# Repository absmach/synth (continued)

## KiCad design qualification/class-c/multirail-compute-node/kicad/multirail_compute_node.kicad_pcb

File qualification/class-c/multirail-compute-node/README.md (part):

# Multi-rail compute node with USB-C and a 5 to 12 V input (Class C, not a case-4 pass)

An STM32F103C8 microcontroller with a 128 Mbit SPI flash and a USB-C receptacle, on a four-layer board of 85.0 x 63.0 mm. It is powered from a 5 to 12 V DC header or from USB VBUS. A 4 A buck converter, three linear rails, a load switch that sequences them and an expansion header complete the board.

It answers #331 under #40: a board whose thermal paths, assembly access and DFM limits are declared and visible in the exported output, made by an agent driving `synth mcp`. It does not claim a case-4 pass. The items in "Not verified by Synth" are open.

The prompt to reproduce the board is in [`PROMPT.md`](PROMPT.md), written from the finished board. The prompts the agent ran are in the history at `72b6f250`.

## The board

### Parts

| Group                | Parts                                                                                                                                                                                                                                                                                                                                                                                      |
| -------------------- | ------------------------------------------------------------------------------------------------------------------------------------------------------------------------------------------------------------------------------------------------------------------------------------------------------------------------------------------------------------------------------------------ |
| DC input (5 to 12 V) | `J2` 1x2 header; `F1` Bourns MF-MSMF110/16-2 (1.1 A hold, 16 V); `D1` Littelfuse SMAJ15A TVS; `D2` Vishay SS36 Schottky reverse-blocking diode (60 V, 0.75 V at 3 A)                                                                                                                                                                                                                       |
| USB input            | `J1` Korean Hroparts TYPE-C-31-M-12 receptacle, flush on the left edge, 5 V only (D+ and D- go to the MCU); `R11` and `R12` 5.1 k CC pull-downs; `F2` Bourns MF-MSMF110/16-2; `D3` Nexperia PTVS6V0S1UR; `D4` Diodes 1N5819HW-7-F ORs VBUS into the buck input (40 V, 450 mV at 1 A); `D5` and `D6` Nexperia PESD5V0S1BA on D+ and D-; `D11` and `D12` the same part on CC1 and CC2; `C30` |
| Buck 3.6 V           | `U1` Texas Instruments LMR33640ADDA (3.8 to 36 V in, 4 A, internal compensation, EN tied to VIN); `L1` Bourns SRN6045TA-6R8M 6.8 uH (Isat 5.7 A, Idc 3.6 A); input `C1`, `C2` 10 uF 25 V and `C3` 220 nF; output `C4`, `C5` 22 uF 25 V; `C6` 100 nF bootstrap; `C7` 1 uF VCC bypass; feedback divider `R2` 10 k and `R3` 3.83 k; `R1` pulls PG up                                          |
| 3.3 V rail           | `U2` TI LP5907MFX-3.3 (3.3 V, 250 mA) with `C8`, `C9`                                                                                                                                                                                                                                                                                                                                      |
| Load switch          | `U5` TI TPS22918DBVR (53 mohm at 3.3 V) with `C12`, `C13` (1 nF, rise time) and `C14`; enable delay `R16` 100 k and `C17` 100 nF                                                                                                                                                                                                                                                           |
| 1.8 V rail           | `U3` Diodes AP2112K-1.8 (600 mA, no minimum load) behind the switch, with `C10`, `C11`                                                                                                                                                                                                                                                                                                     |
| 1.2 V rail           | `U4` TI TLV70012DDCR (1.2 V, 200 mA, DDC package) enabled by the 1.8 V rail, with `C15`, `C16`                                                                                                                                                                                                                                                                                             |
| Compute core         | `U6` STMicroelectronics STM32F103C8T6 (LQFP-48) with decoupling `C20` to `C25`; `Y1` JYJE 3TJ480000FYLBC 8 MHz crystal with `C26`, `C27` 10 pF; reset `R9`, `C28`, `SW1`; `R10` pulls BOOT0 low; `R13` 1.5 k USB D+ pull-up; `J3` 1x5 SWD header                                                                                                                                           |
| Memory               | `U7` Winbond W25Q128JVSIQ, SOIC-8 208 mil, on SPI1 (`PA4` to `PA7`) with `C29`, `R14`, `R15`                                                                                                                                                                                                                                                                                               |
| Indicators           | `D7` red (3.6 V), `D8` green (3.3 V), `D9` and `D10` yellow user LEDs, with `R5` to `R8`                                                                                                                                                                                                                                                                                                   |
| Expansion            | `J4` Harwin M20-9990846 1x8 header: 3.6 V gated, 3.3 V, 1.8 V, 1.2 V, two GPIOs, two grounds                                                                                                                                                                                                                                                                                               |
| Fabrication features | Test points `TP1` to `TP9`, all on the bottom side of the board; fiducials `FID1` to `FID3`; two M2.5 mounting holes at opposite corners, each 4.0 mm from its two board edges                                                                                                                                                                                                                                                                                                            |

### Layout

| Item                    | Value                                                                                                                                                                         |
| ----------------------- | ----------------------------------------------------------------------------------------------------------------------------------------------------------------------------- |
| Outline                 | 85.0 x 63.0 mm, declared in the source (`outline 85mm x 63mm`)                                                                                                                                                                |
| Copper layers           | 4                                                                                                                                                                             |
| Stackup                 | 1.59 mm total (board file); `manufacturer "jlc-filled-via"` with `requires via_in_pad` (resin-filled, capped vias for the exposed-pad vias); JLCPCB 7628 stack, 1.065 mm core |
| Parts in the BOM        | 85 lines: 71 parts and 14 board features (test points, fiducials, mounting holes)                                                                                             |
| Parts placed in the CPL | 74                                                                                                                                                                            |
| Nets                    | 42, all routed                                                                                                                                                                |
| Track segments          | 456                                                                                                                                                                           |
| Vias                    | 88: 21 x 0.46/0.2 mm and 67 x 0.6/0.3 mm                                                                                                                                      |
| Track length            | 1270.8 mm                                                                                                                                                                     |
| Zones and planes        | `GND` poured on all four layers; the rails are tracks, not planes; `hot_buck` keepout rule area on `U1`; 2.75 mm screw-head zones on `H1` and `H2`                            |
| Fab package             | `fab/gerbers.zip` (16 files), `fab/bom.csv`, `fab/cpl.csv`; every file is in `SHA256SUMS`                                                                                     |
| 3D models               | `models/` holds the STEP body of every part the board references and the board model `multirail_compute_node.step`. The board file reaches them by the relative path `${KIPRJMOD}/../models/`. Mounting holes and fiducials have no body. `J1` uses the HRO TYPE-C-31-M-12 STEP from github.com/ai03-2725/Type-C.pretty (the repository states no licence), placed to match KiCad's footprint. Any other part that KiCad's library has no model for is a simplified box of its envelope. |
| Schematic               | `images/schematic.pdf`: vector pages, one per sheet, plotted by `kicad-cli sch export pdf`. |

### Checks

| Check                              | Result                               | Notes                                                                                                 |
| ---------------------------------- | ------------------------------------ | ----------------------------------------------------------------------------------------------------- |
| KiCad DRC (10.0.8, --refill-zones) | 0 errors, 7 warnings, 0 unconnected  | The warnings are 4 `silk_over_copper` and 3 `lib_footprint_mismatch` on the fiducials                                                                 |
| KiCad ERC (10.0.8)                 | 0 errors, 63 warnings, 0 unconnected | 62 `lib_symbol_issues`, 1 `lib_symbol_mismatch`                                                       |
| KiCad DRC with the library tables  | 85 `lib_footprint_mismatch`          | The exporter cuts back the silkscreen (#425); pads and courtyards match the library                   |
| Gerbers                            | Plotted from refilled zones          | Plotted from the refilled zones of the committed board                                                |
| `synth validate`                   | 0 errors, 40 warnings                | 17 are schematic-layout findings: 9 `E-SYNTH-SCHEM-003`, 7 `E-SYNTH-SCHEM-001`, 1 `E-SYNTH-SCHEM-004` |
| Schematic-layout findings          | Accepted as a group                  | They concern the drawing of the generated schematic, not the netlist or the board                     |
| `synth validate` warning count     | Varies                               | The count changes with the Synth version                                                              |

### Design figures

| Area             | Item                     | Value                                                                                                                                                                | Basis                                                                              |
| ---------------- | ------------------------ | -------------------------------------------------------------------------------------------------------------------------------------------------------------------- | ---------------------------------------------------------------------------------- |
| Protection       | `D1` standoff            | 15 V, above the 12.6 V maximum input (12 V +5 %)                                                                                                                     | Littelfuse SMAJ15A datasheet; calculated                                           |
| Protection       | `D1` clamp               | 24.4 V at 16.4 A, below the 36 V input maximum of `U1`                                                                                                               | Littelfuse SMAJ15A and TI LMR33640 datasheets                                      |
| Protection       | `D3` standoff            | 6.0 V, above the 5.25 V maximum VBUS                                                                                                                                 | Nexperia PTVS6V0S1UR datasheet                                                     |
| Power            | Buck output voltage      | 1.0 V x (1 + 10 / 3.83) = 3.611 V                                                                                                                                    | Calculated; 1.0 V feedback reference from the TI LMR33640 datasheet                |
| Power            | Inductor ripple          | (12 - 3.611) x (3.611 / 12) / (6.8 uH x 400 kHz) = 0.93 A at 12 V in, 400 kHz                                                                                        | Calculated                                                                         |
| Power            | Load switch enable delay | `R16` 100 k x `C17` 100 nF = 10 ms                                                                                                                                   | Calculated                                                                         |
| Power            | Rail sequence            | 3.3 V first; then the switch passes 3.6 V to the 1.8 V regulator; then 1.8 V enables the 1.2 V regulator                                                             | Netlist in the .synth source                                                       |
| Power            | Sequenced rail loads     | The 1.8 V and 1.2 V rails feed only `J4` and test points; the STM32F103C8 runs from 3.3 V alone, so the sequencing protects no device on this board                  | Netlist in the .synth source                                                       |
| Power            | USB-only input to `U1`   | At 4.75 V VBUS and 1.0 A, `F2` (0.21 ohm) drops 0.21 V and `D4` drops 0.45 V, so `U1` sees 4.09 V                                                                    | Calculated                                                                         |
| Power            | USB-only buck margin     | `U1` needs 3.76 V for a 3.611 V output (150 mV dropout at 1 A); margin 0.33 V                                                                                        | TI LMR33640 datasheet; calculated                                                  |
| Power            | USB-only LDO margin      | The LP5907 needs 3.55 V (250 mV dropout at 250 mA); margin 61 mV                                                                                                     | TI LP5907 datasheet; calculated                                                    |
| Power            | Power good               | `PG_3V6` goes to `PA0` of `U6`, pulled up by `R1` 10 k to `V3V3` (0.33 mA when low)                                                                                  | Calculated                                                                         |
| Thermal          | Method                   | Tj = TA + P x RthetaJA, with the datasheet JEDEC RthetaJA; rails run from the 3.611 V buck output; current limit is the load at which Tj reaches 125 C               | Calculated                                                                         |
| Thermal          | `U2` LP5907 3.3 V        | Drop 0.311 V; 78 mW at 250 mA, +15 K; not limiting                                                                                                                   | TI LP5907 datasheet, RthetaJA 193.4 C/W (DBV)                                      |
| Thermal          | `U3` AP2112K-1.8         | Drop 1.811 V; 1.09 W at 600 mA, beyond 125 C; limit 0.23 A at 50 C, 0.12 A at 85 C                                                                                   | Diodes AP2112 datasheet, RthetaJA 184 C/W (SOT-25)                                 |
| Thermal          | `U4` TLV70012 1.2 V      | Drop 2.411 V; 482 mW at 200 mA, beyond 125 C; limit 0.118 A at 50 C, 0.063 A at 85 C                                                                                 | TI TLV700 datasheet, RthetaJA 262.8 C/W (DDC)                                      |
| Thermal          | `U5` TPS22918            | Loss 53 mohm x I^2; 53 mW at 1 A, +9.7 K; not limiting                                                                                                               | TI TPS22918 datasheet, RthetaJA 183.2 C/W (DBV)                                    |
| Thermal          | External load on `J4`    | The 1.8 V and 1.2 V limits above are the currents an external load on `J4` may draw                                                                                  | Calculated                                                                         |
| Thermal          | `U1` thermal vias        | Exposed pad 2.41 x 3.1 mm (`GND`) carries six 0.46/0.2 mm vias at 1.2 mm pitch, as `[[vias]]` entries of the placement sidecar; Synth has no thermal-array statement | Measured on the board file; TI LMR33640 datasheet, section 9.5.1.1, asks for 4 x 3 |
| Thermal          | `hot_buck` keepout       | 5 mm ring anchored on `U1`, exported as a rule area; its `allow` list holds the buck nets plus `GND` and `V3V6`, so it is not a copper-free ring                     | .synth source; measured on the board file                                          |
| Signal integrity | USB pair                 | Full speed only; both lines on `F.Cu`; 95.3 mm (D+) and 70.5 mm (D-)                                                                                                | Measured on the board file                                                         |
| Signal integrity | USB skew                 | The 19.1 mm difference is about 105 ps against a 4 ns minimum edge; the `USB` class declares `edge_rate medium`; no `diff_pair` is declared                          | Calculated                                                                         |
| Signal integrity | Net classes              | `PWR` 0.6 mm (about 1.6 A), `PWR_LOW` 0.3 mm (about 1.0 A), `GNDC` 0.4 mm, `BUCK_SW` 0.6 mm on `F.Cu`, signals 0.2 mm                                                | IPC-2221, 10 K rise; .synth source                                                 |
| Signal integrity | Return vias              | `XTAL`, `SPI` and `USB` are locked to `F.Cu`, so they need no return via                                                                                             | .synth source                                                                      |
| Assembly         | Connector on its edge    | `J1` courtyard 0.1 mm from Edge.Cuts                                                                                                                                 | Measured on the board file                                                         |
| Assembly         | Headers inboard          | `J3` 0.74 mm, `J4` 2.73 mm, `J2` 2.73 mm from the edge                                                                                                               | Measured on the board file                                                         |
| Assembly         | Other parts              | The four LEDs 4.77 mm from the edge, everything else further                                                                                                         | Measured on the board file                                                         |
| Assembly         | Through-hole to SMD pad  | At least 2.58 mm (`J3` pin 5 to `TP8`); the JLCPCB rule is 2.1 mm                                                                                                    | Measured on the board file                                                         |
| Assembly         | Fiducials                | `FID1` to `FID3`, 1 mm with a 2 mm mask opening                                                                                                                      | Measured on the board file                                                         |
| Assembly         | Mounting holes           | Nearest courtyard 11.2 mm from `H1` and 13.4 mm from `H2`                                                                                                            | Measured on the board file                                                         |
| Assembly         | Via rings                | 0.13 mm (0.46/0.2 mm) and 0.15 mm (0.6/0.3 mm), at the `jlc-filled-via` floors                                                                                       | Measured on the board file                                                         |

### Sourcing

| Item                         | Status                      | Notes                                                                                                                                                                                                                                   |
| ---------------------------- | --------------------------- | --------------------------------------------------------------------------------------------------------------------------------------------------------------------------------------------------------------------------------------- |
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
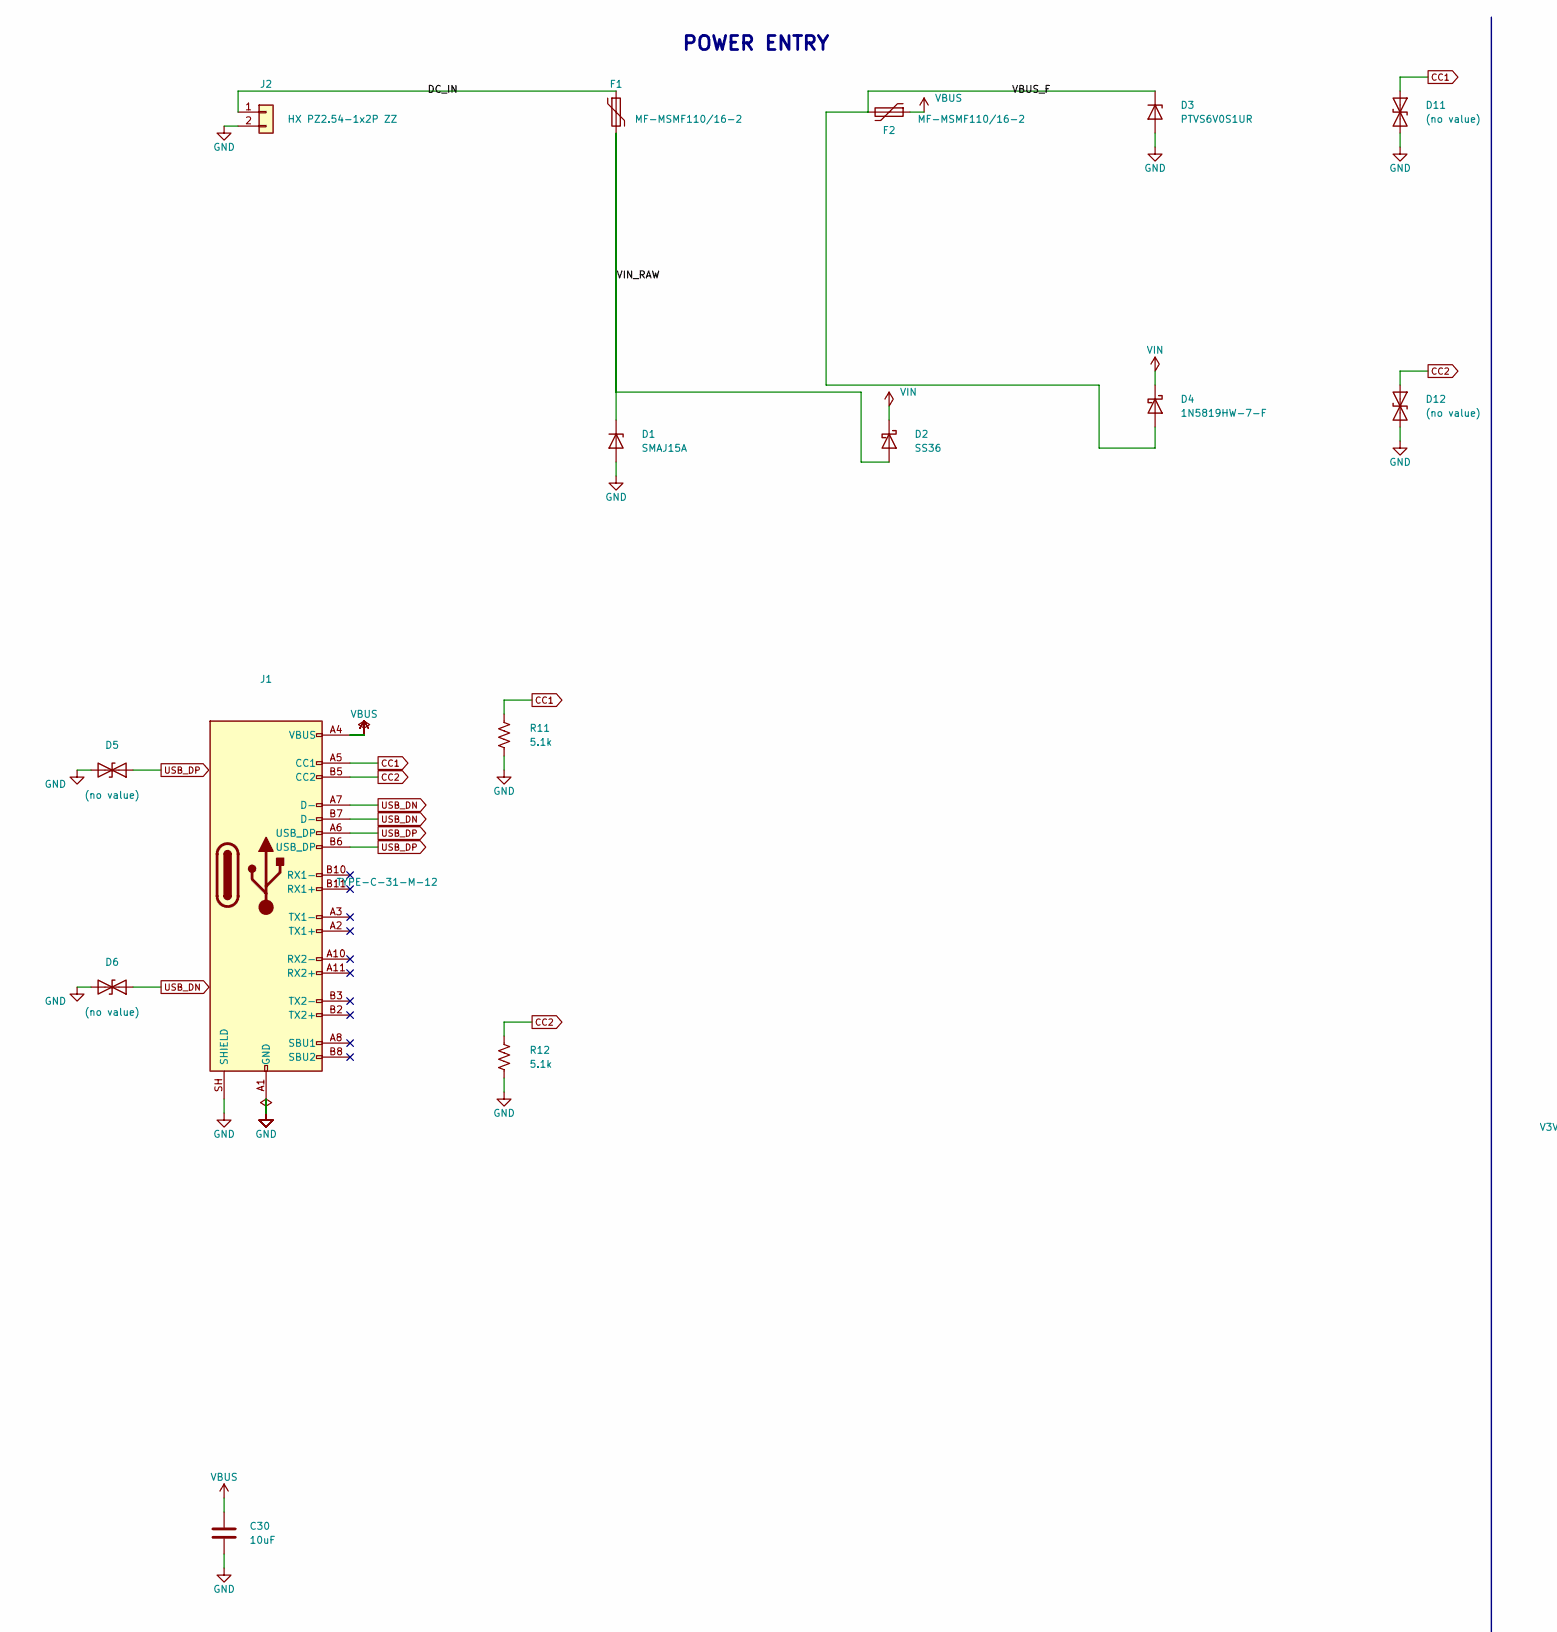
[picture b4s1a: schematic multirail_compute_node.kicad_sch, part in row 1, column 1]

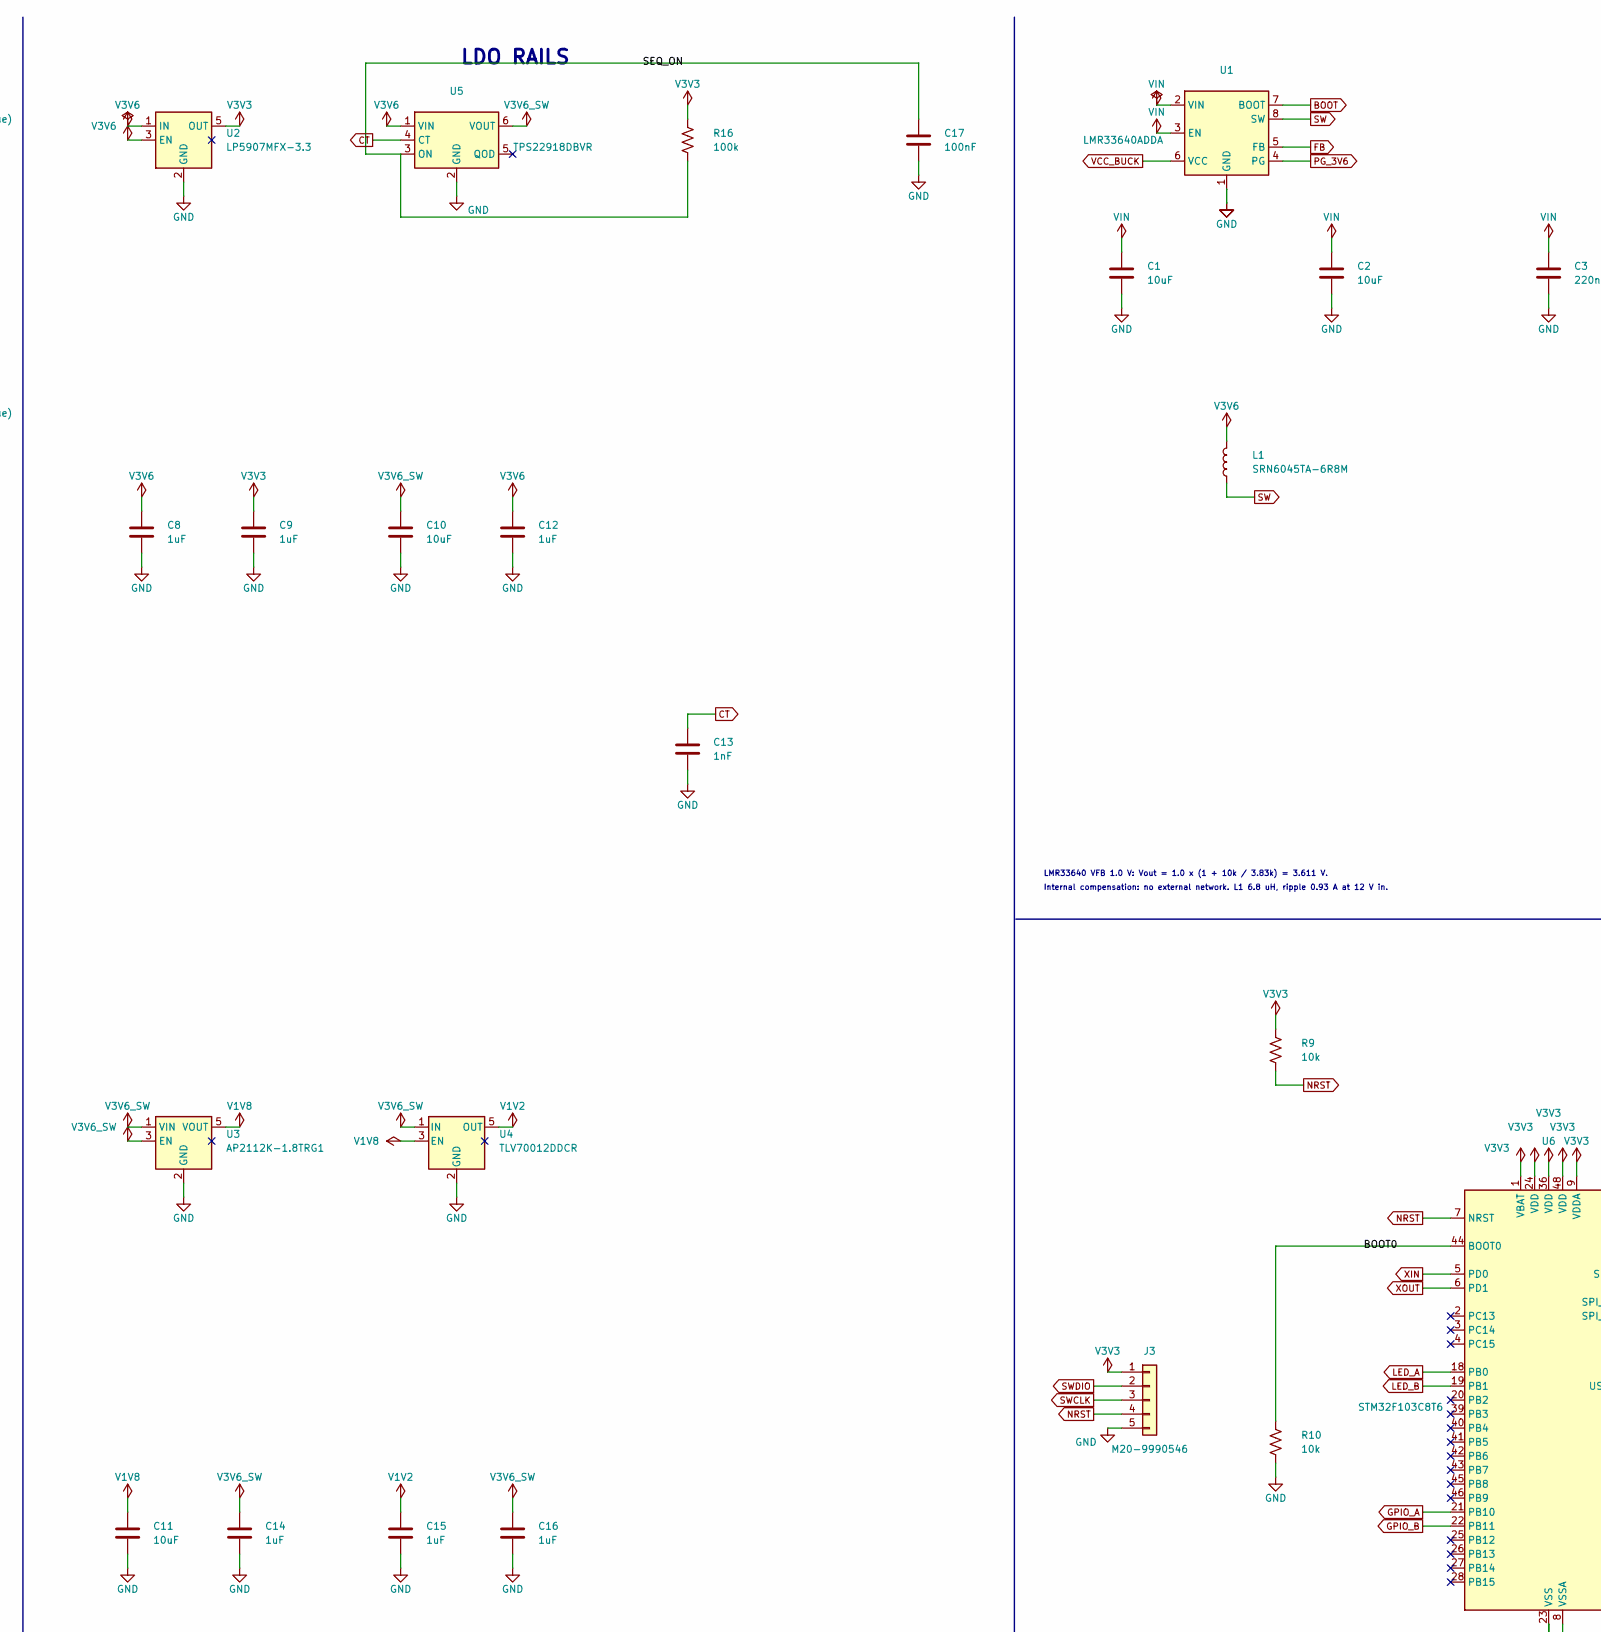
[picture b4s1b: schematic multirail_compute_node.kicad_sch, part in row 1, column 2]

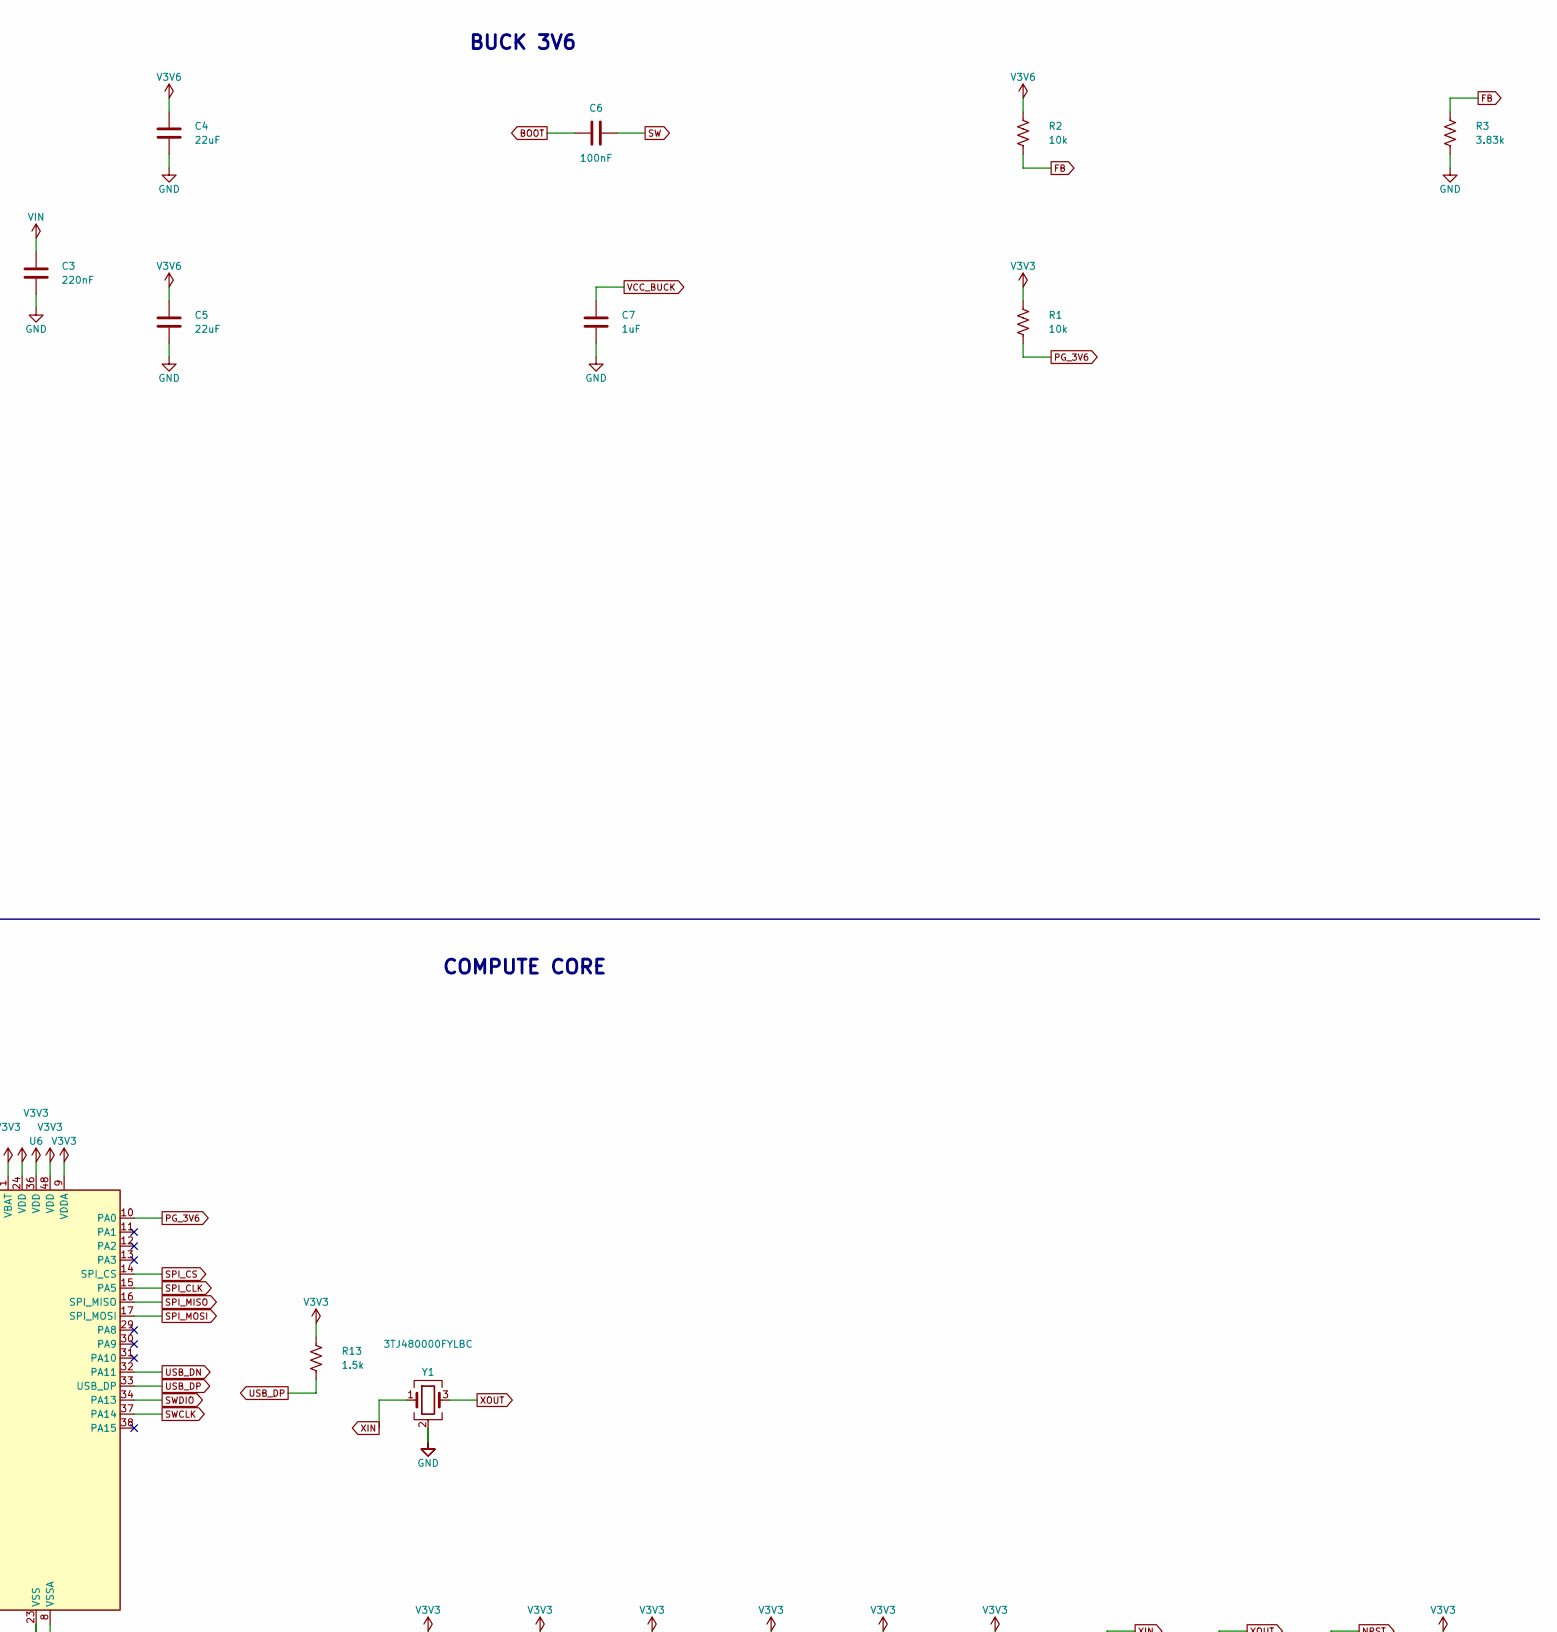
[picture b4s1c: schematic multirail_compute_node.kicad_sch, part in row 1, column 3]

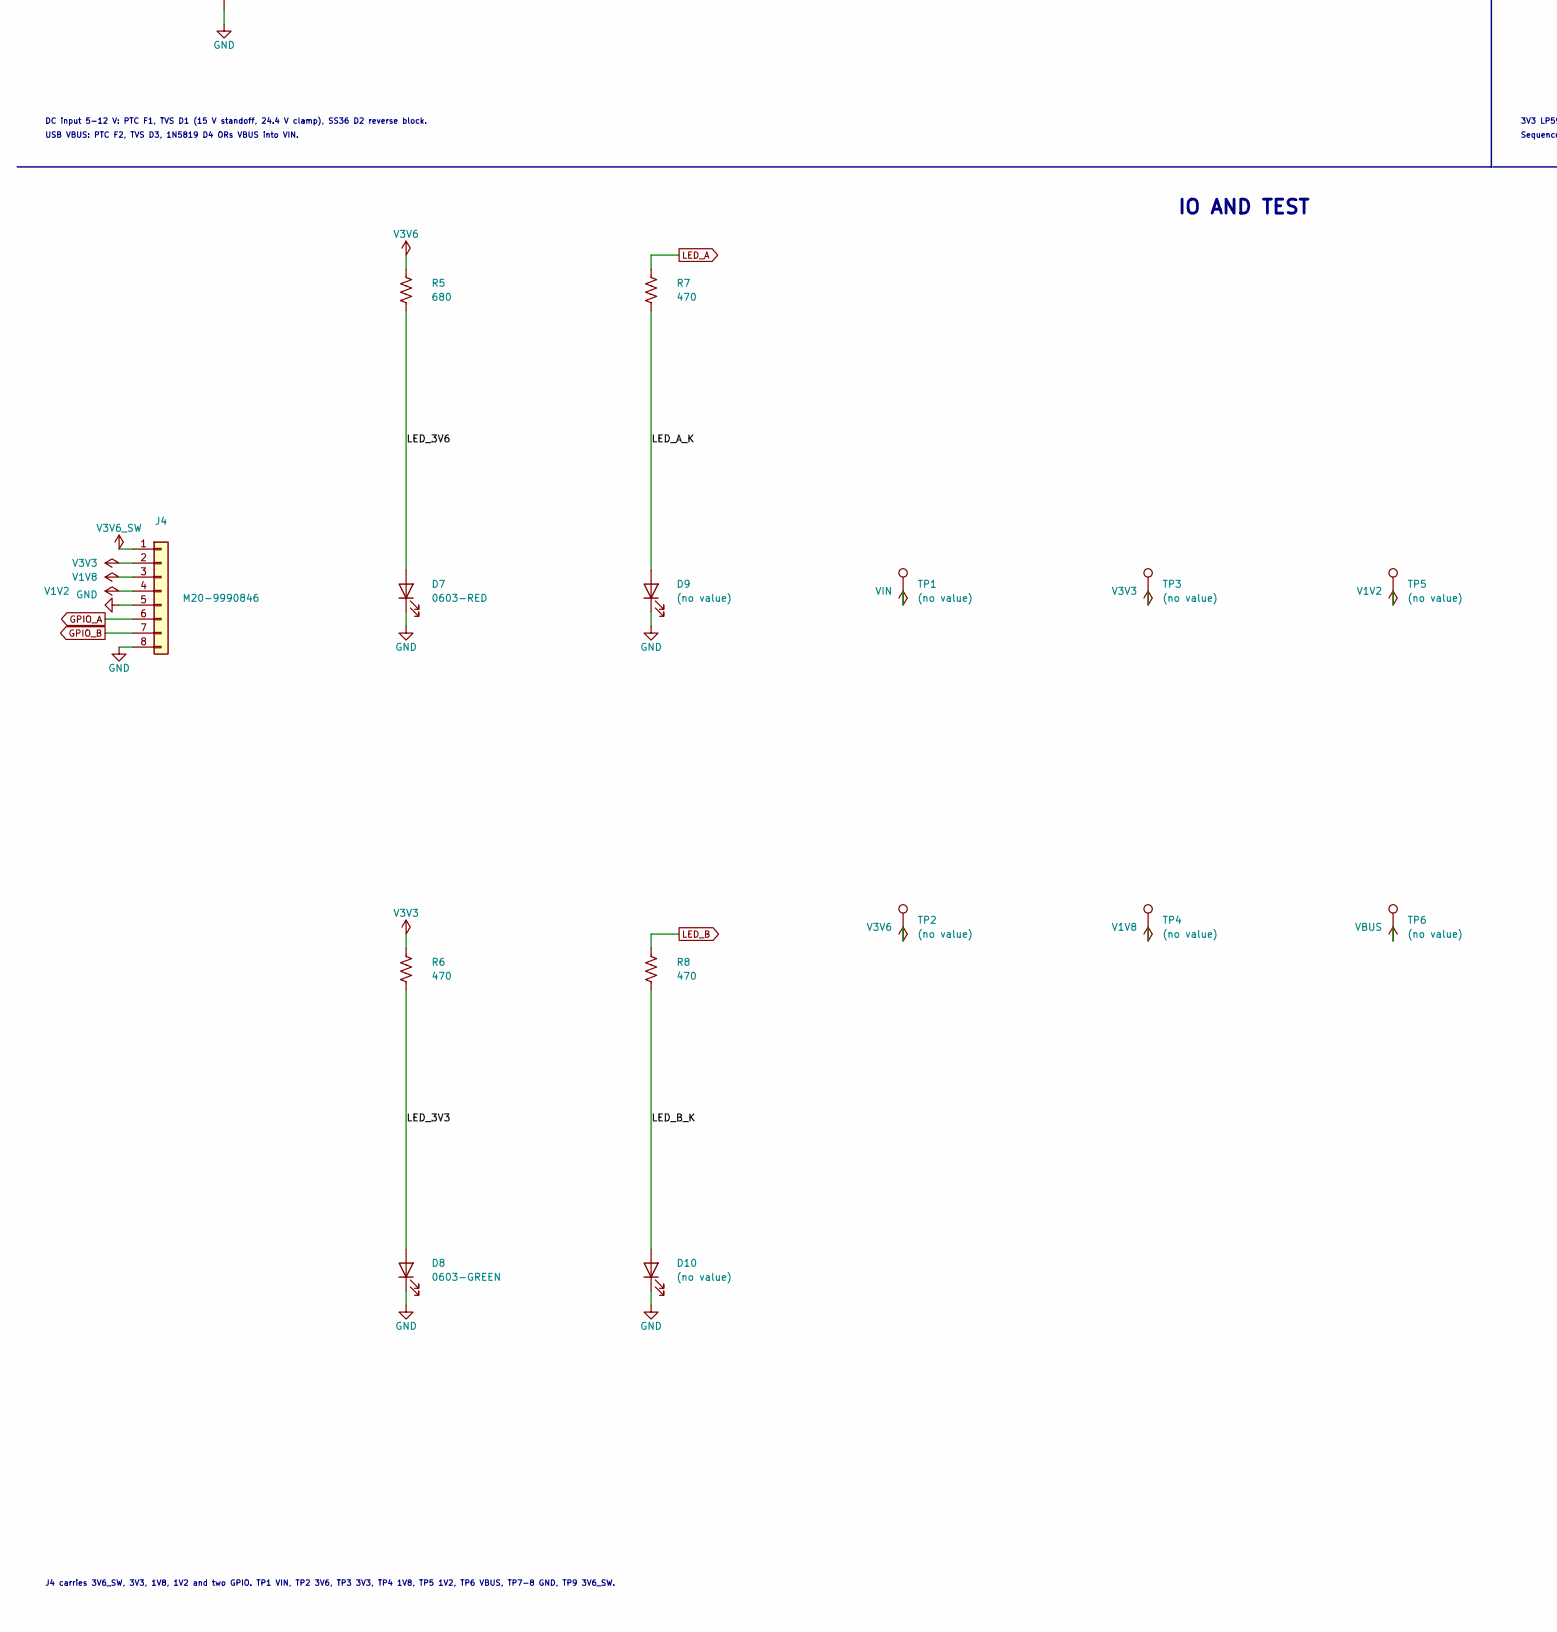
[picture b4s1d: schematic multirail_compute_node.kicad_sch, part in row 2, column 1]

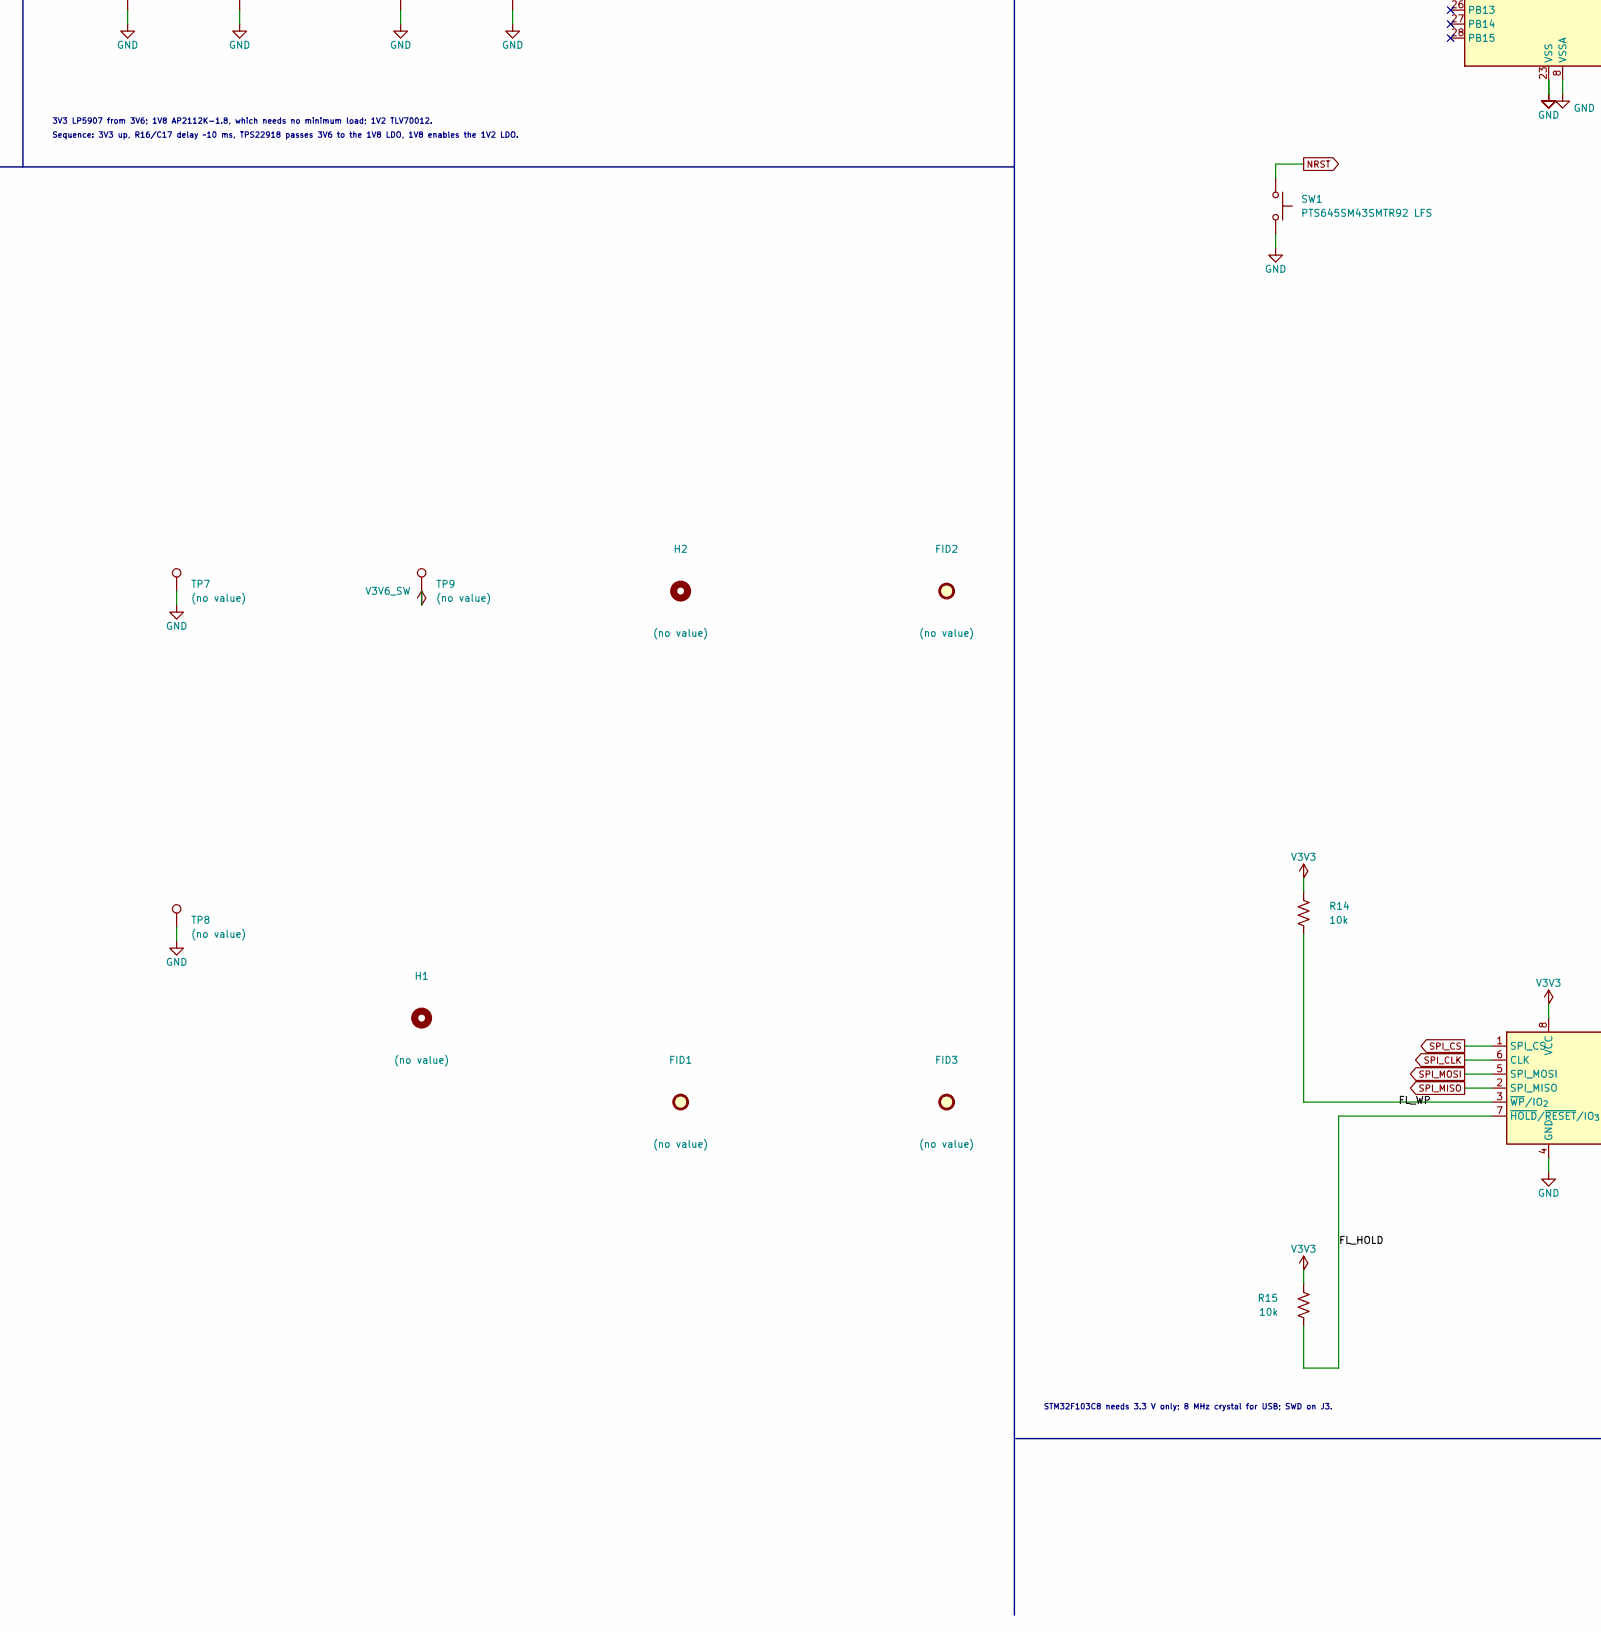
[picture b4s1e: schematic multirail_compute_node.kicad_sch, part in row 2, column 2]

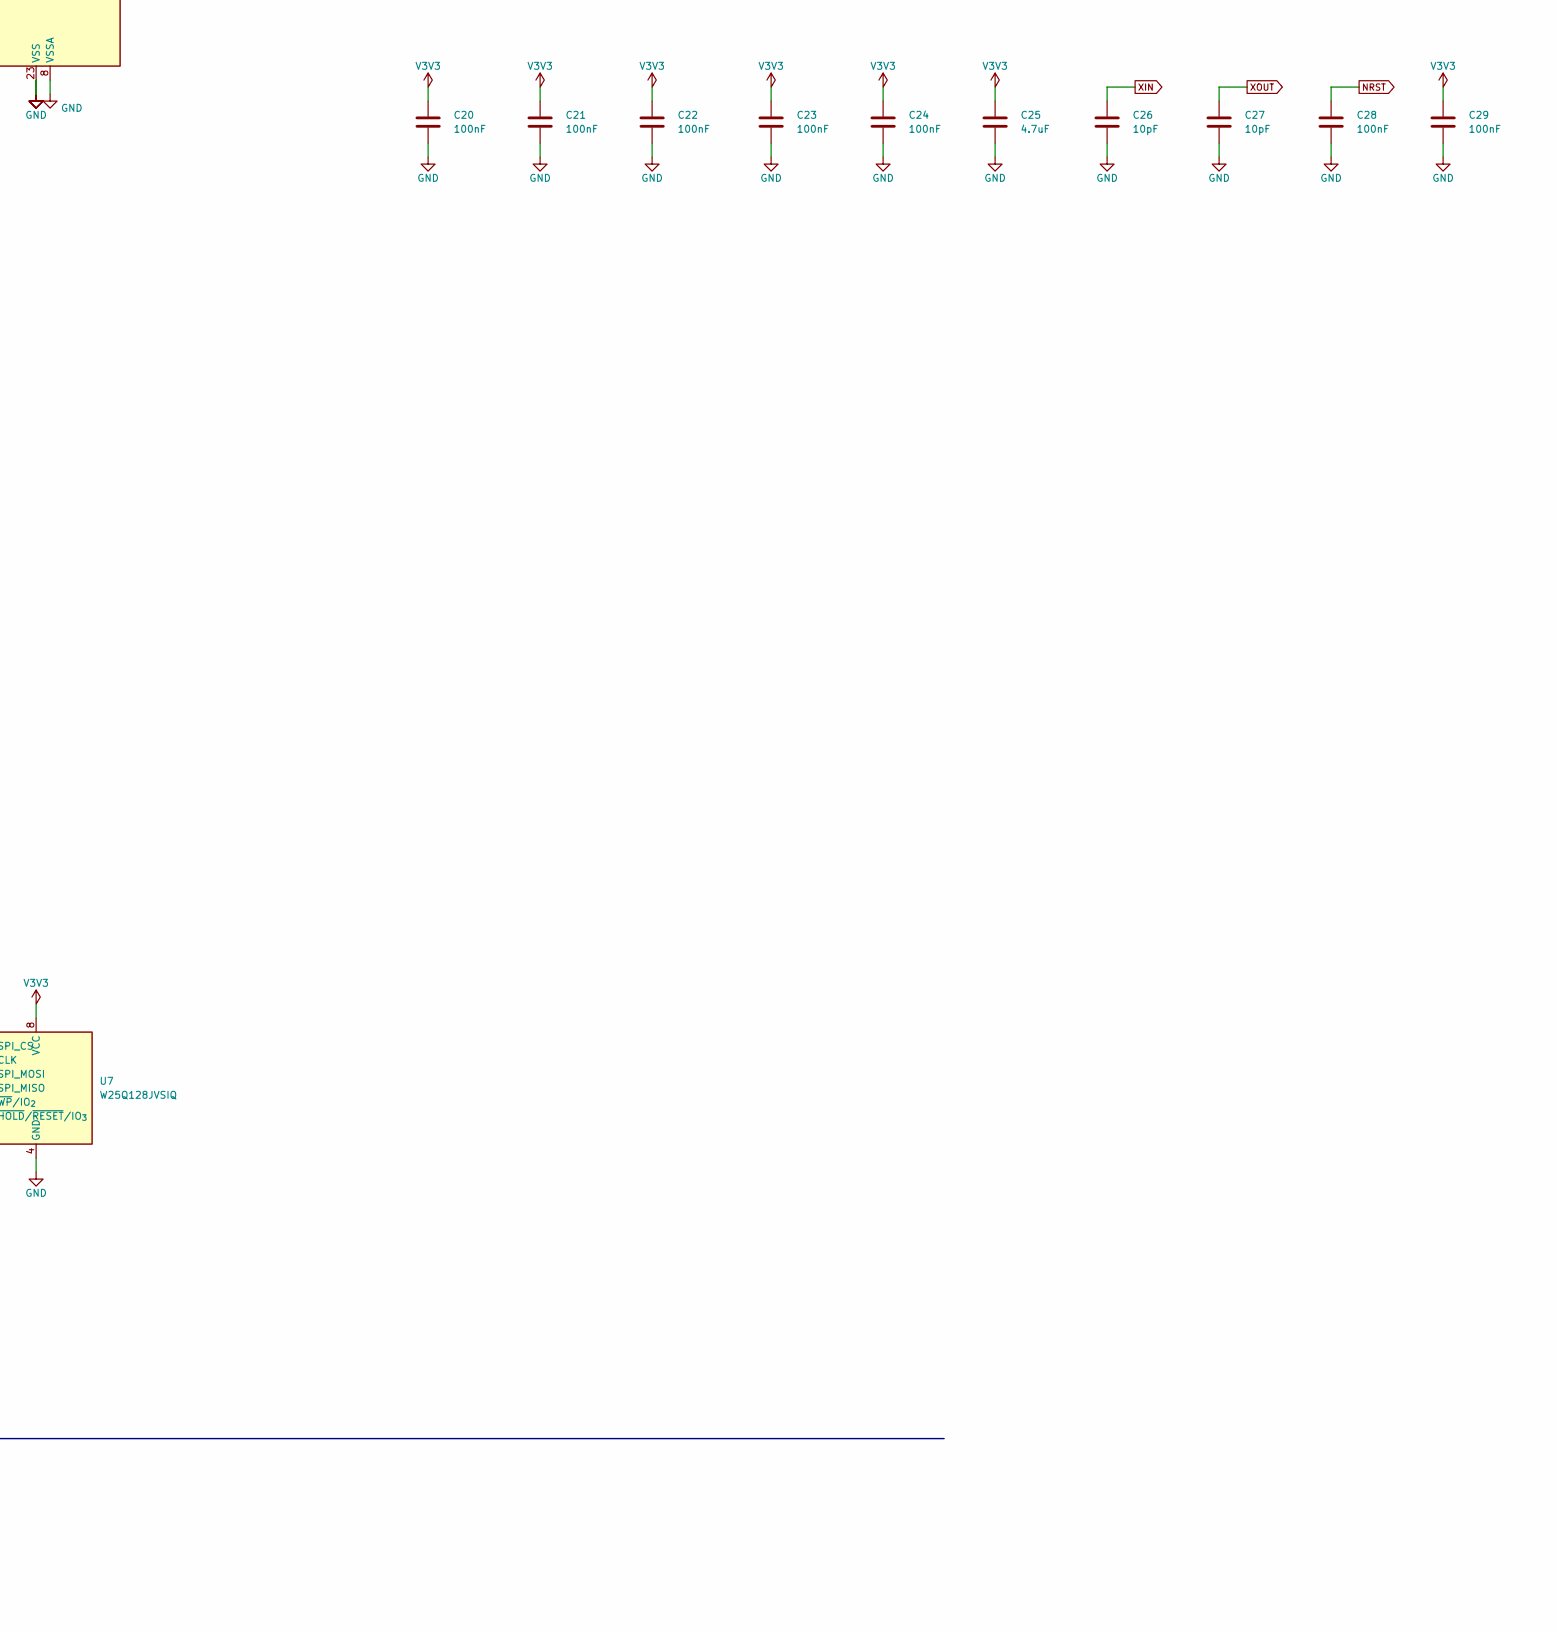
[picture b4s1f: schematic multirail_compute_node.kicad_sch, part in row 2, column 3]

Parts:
C1, C2: 10uF; C_1206_3216Metric
C3: 220nF; C_0603_1608Metric
C4, C5: 22uF; C_0805_2012Metric
C6, C17, C20, C21, C22, C23, C24, C28, C29: 100nF; C_0603_1608Metric
C7, C8, C9, C12, C14, C15, C16: 1uF; C_0603_1608Metric
C10, C11, C30: 10uF; C_0805_2012Metric
C13: 1nF; C_0603_1608Metric
C25: 4.7uF; C_0805_2012Metric
C26, C27: 10pF; C_0603_1608Metric
D1: SMAJ15A; D_SMA; MPN SMAJ15A; LCSC C148216
D2: SS36; D_SMC; MPN SS36
D3: PTVS6V0S1UR; Nexperia_CFP3_SOD-123W; MPN PTVS6V0S1UR
D4: 1N5819HW-7-F; D_SOD-123; MPN 1N5819HW-7-F; LCSC C82544
D5, D6, D11, D12: (no value); D_SOD-323
D7: 0603-RED; LED_0603_1608Metric; MPN 0603-RED; LCSC C2286
D8: 0603-GREEN; LED_0603_1608Metric; MPN 0603-GREEN; LCSC C72043
D9, D10: (no value); LED_0603_1608Metric
F1, F2: MF-MSMF110/16-2; Fuse_1812_4532Metric; MPN MF-MSMF110/16-2; LCSC C210834
FID1, FID2, FID3: (no value); Fiducial_1mm_Mask2mm
H1, H2: (no value); MountingHole_2.5mm
J1: TYPE-C-31-M-12; USB_C_Receptacle_HRO_TYPE-C-31-M-12; MPN TYPE-C-31-M-12; LCSC C165948
J2: HX PZ2.54-1x2P ZZ; PinHeader_1x02_P2.54mm_Vertical; MPN HX PZ2.54-1x2P ZZ; LCSC C32713268
J3: M20-9990546; PinHeader_1x05_P2.54mm_Vertical; MPN M20-9990546; LCSC C3328227
J4: M20-9990846; PinHeader_1x08_P2.54mm_Vertical; MPN M20-9990846
L1: SRN6045TA-6R8M; L_Bourns_SRN6045TA; MPN SRN6045TA-6R8M
R1, R2, R9, R10, R14, R15: 10k; R_0603_1608Metric
R3: 3.83k; R_0603_1608Metric
R5: 680; R_0603_1608Metric
R6, R7, R8: 470; R_0603_1608Metric
R11, R12: 5.1k; R_0603_1608Metric
R13: 1.5k; R_0603_1608Metric
R16: 100k; R_0603_1608Metric
SW1: PTS645SM43SMTR92 LFS; SW_SPST_PTS645Sx43SMTR92; MPN PTS645SM43SMTR92 LFS; LCSC C221880
TP1, TP2, TP3, TP4, TP5, TP6, TP7, TP8, TP9: (no value); TestPoint_Pad_D1.5mm
U1: LMR33640ADDA; HSOP-8-1EP_3.9x4.9mm_P1.27mm_EP2.41x3.1mm; MPN LMR33640ADDA
U2: LP5907MFX-3.3; SOT-23-5; MPN LP5907MFX-3.3; LCSC C83437
U3: AP2112K-1.8TRG1; SOT-23-5; MPN AP2112K-1.8TRG1; LCSC C176944
U4: TLV70012DDCR; TSOT-23-5; MPN TLV70012DDCR; LCSC C69446
U5: TPS22918DBVR; SOT-23-6; MPN TPS22918DBVR; LCSC C131941
U6: STM32F103C8T6; LQFP-48_7x7mm_P0.5mm; MPN STM32F103C8T6; LCSC C8734
U7: W25Q128JVSIQ; SOIC-8_5.3x5.3mm_P1.27mm; MPN W25Q128JVSIQ; LCSC C97521
Y1: 3TJ480000FYLBC; Crystal_SMD_3225-4Pin_3.2x2.5mm; MPN 3TJ480000FYLBC

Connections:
BOOT: C6.1, U1.7 (BOOT)
BOOT0: R10.1, U6.44 (BOOT0)
CC1: D11.1 (A1), J1.A5 (CC1), R11.1
CC2: D12.1 (A1), J1.B5 (CC2), R12.1
CT: C13.1, U5.4 (CT)
DC_IN: F1.1, J2.1
FB: R2.2, R3.1, U1.5 (FB)
FL_HOLD: R15.1, U7.7 (~HOLD/~RESET/IO_{3})
FL_WP: R14.1, U7.3 (~WP/IO_{2})
GND: C1.2, C2.2, C3.2, C4.2, C5.2, C7.2, C8.2, C9.2, C10.2, C11.2, C12.2, C13.2, C14.2, C15.2, C16.2, C17.2, C20.2, C21.2, C22.2, C23.2, C24.2, C25.2, C26.2, C27.2, C28.2, C29.2, C30.2, D1.2 (A), D3.2 (A), D5.2 (A2), D6.2 (A2), D7.1 (K), D8.1 (K), D9.1 (K), D10.1 (K), D11.2 (A2), D12.2 (A2), J1.A1 (GND), J1.A12 (GND), J1.B1 (GND), J1.B12 (GND), J1.SH (SHIELD), J2.2, J3.5, J4.5, J4.8, R3.2, R10.2, R11.2, R12.2, SW1.2, TP7.1, TP8.1, U1.1 (GND), U1.9 (GND), U2.2 (GND), U3.2 (GND), U4.2 (GND), U5.2 (GND), U6.8 (VSSA), U6.23 (VSS), U6.35 (VSS), U6.47 (VSS), U7.4 (GND), Y1.2 (G), Y1.4 (G)
GPIO_A: J4.6, U6.21 (PB10)
GPIO_B: J4.7, U6.22 (PB11)
LED_3V3: D8.2 (A), R6.2
LED_3V6: D7.2 (A), R5.2
LED_A: R7.1, U6.18 (PB0)
LED_A_K: D9.2 (A), R7.2
LED_B: R8.1, U6.19 (PB1)
LED_B_K: D10.2 (A), R8.2
NRST: C28.1, J3.4, R9.2, SW1.1, U6.7 (NRST)
PG_3V6: R1.1, U1.4 (PG), U6.10 (PA0)
SEQ_ON: C17.1, R16.2, U5.3 (ON)
SPI_CLK: U6.15 (PA5), U7.6 (CLK)
SPI_CS: U6.14 (PA4), U7.1 (~CS)
SPI_MISO: U6.16 (PA6), U7.2 (DO/IO_{1})
SPI_MOSI: U6.17 (PA7), U7.5 (DI/IO_{0})
SW: C6.2, L1.1, U1.8 (SW)
SWCLK: J3.3, U6.37 (PA14)
SWDIO: J3.2, U6.34 (PA13)
USB_DN: D6.1 (A1), J1.A7 (D-), J1.B7 (D-), U6.32 (PA11)
USB_DP: D5.1 (A1), J1.A6 (D+), J1.B6 (D+), R13.2, U6.33 (PA12)
V1V2: C15.1, J4.4, TP5.1, U4.5 (OUT)
V1V8: C11.1, J4.3, TP4.1, U3.5 (VOUT), U4.3 (EN)
V3V3: C9.1, C20.1, C21.1, C22.1, C23.1, C24.1, C25.1, C29.1, J3.1, J4.2, R1.2, R6.1, R9.1, R13.1, R14.2, R15.2, R16.1, TP3.1, U2.5 (OUT), U6.1 (VBAT), U6.9 (VDDA), U6.24 (VDD), U6.36 (VDD), U6.48 (VDD), U7.8 (VCC)
V3V6: C4.1, C5.1, C8.1, C12.1, L1.2, R2.1, R5.1, TP2.1, U2.1 (IN), U2.3 (EN), U5.1 (VIN)
V3V6_SW: C10.1, C14.1, C16.1, J4.1, TP9.1, U3.1 (VIN), U3.3 (EN), U4.1 (IN), U5.6 (VOUT)
VBUS: C30.1, F2.1, J1.A4 (VBUS), J1.A9 (VBUS), J1.B4 (VBUS), J1.B9 (VBUS), TP6.1
VBUS_F: D3.1 (K), D4.2 (A), F2.2
VCC_BUCK: C7.1, U1.6 (VCC)
VIN: C1.1, C2.1, C3.1, D2.1 (K), D4.1 (K), TP1.1, U1.2 (VIN), U1.3 (EN)
VIN_RAW: D1.1 (K), D2.2 (A), F1.2
XIN: C26.1, U6.5 (PD0), Y1.1
XOUT: C27.1, U6.6 (PD1), Y1.3

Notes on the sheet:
POWER ENTRY
BUCK 3V6
LDO RAILS
COMPUTE CORE
IO AND TEST
DC input 5-12 V: PTC F1, TVS D1 (15 V standoff, 24.4 V clamp), SS36 D2 reverse block.
USB VBUS: PTC F2, TVS D3, 1N5819 D4 ORs VBUS into VIN.
LMR33640 VFB 1.0 V: Vout = 1.0 x (1 + 10k / 3.83k) = 3.611 V.
Internal compensation: no external network. L1 6.8 uH, ripple 0.93 A at 12 V in.
3V3 LP5907 from 3V6; 1V8 AP2112K-1.8, which needs no minimum load; 1V2 TLV70012.
Sequence: 3V3 up, R16/C17 delay ~10 ms, TPS22918 passes 3V6 to the 1V8 LDO, 1V8 enables the 1V2 LDO.
STM32F103C8 needs 3.3 V only; 8 MHz crystal for USB; SWD on J3.
J4 carries 3V6_SW, 3V3, 1V8, 1V2 and two GPIO. TP1 VIN, TP2 3V6, TP3 3V3, TP4 1V8, TP5 1V2, TP6 VBUS, TP7-8 GND, TP9 3V6_SW.
